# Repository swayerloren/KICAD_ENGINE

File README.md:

# KiCad Engine

AI-assisted KiCad workflow engine for using Codex or Claude inside VS Code with your existing KiCad app.

KiCad Engine is a repo you can download, open in VS Code, and give to Codex or Claude so the AI agent has structured rules, prompts, tools, and workflows for working on KiCad schematic and PCB projects. It is designed for people who already like KiCad and want AI assistance without switching to Flux or another paid PCB design platform.

The repo is the AI-agent operating system for KiCad work. It gives the agent a repeatable workspace, startup rules, task contracts, validation gates, and project structure so it can help with real KiCad projects without depending on hidden local folders or improvised workflow assumptions.

Historical reports may still show original local paths; current work must use repo-relative paths and live discovery on the user's machine.

## Fast Start: ZIP -> VS Code -> One Prompt

1. Download the repo ZIP from GitHub.
2. Extract it.
3. Open the `KICAD_ENGINE` folder in VS Code.
4. Open Codex or Claude in that workspace.
5. Paste this minimal prompt:

```text
Read START_HERE_FOR_AI_AGENTS.md and route yourself correctly. Use the task router automatically if I do not provide a giant read-first list. Do not edit KiCad schematic or PCB files until the active project, task type, and relevant gates are confirmed. Summarize the current repo/project status and ask what task to run next.
```

Useful follow-up docs:

- [ONE_PROMPT_START.md](ONE_PROMPT_START.md)
- [DOWNLOAD_ZIP_START_HERE.md](DOWNLOAD_ZIP_START_HERE.md)
- [START_HERE.md](START_HERE.md)
- [CURRENT_STATUS.md](CURRENT_STATUS.md)
- [PROJECTS_INDEX.md](PROJECTS_INDEX.md)
- [WORKFLOWS_INDEX.md](WORKFLOWS_INDEX.md)
- [TOOLS_INDEX.md](TOOLS_INDEX.md)
- [03_TOOLS/TOOLS_INDEX.md](03_TOOLS/TOOLS_INDEX.md)
- [EXTERNAL_DEPENDENCIES.md](EXTERNAL_DEPENDENCIES.md)
- [LOCAL_SETUP_REQUIREMENTS.md](LOCAL_SETUP_REQUIREMENTS.md)
- [docs/PATH_PORTABILITY.md](docs/PATH_PORTABILITY.md)
- [docs/HEALTH_CHECK.md](docs/HEALTH_CHECK.md)

## Optional Open-Source Tool Integrations

KiCad Engine now includes a first-party optional-tool integration layer under
[`03_TOOLS/open_source_integrations`](03_TOOLS/open_source_integrations/README.md).

- It documents approved upstream tools and their licenses.
- It keeps the default ZIP download usable without large bundled payloads.
- It provides dry-run install wrappers and a read-only verification script.
- It does not vendor upstream repos, `node_modules`, virtual environments, or
  large binaries by default.

Useful entry points:

- [`03_TOOLS/open_source_integrations/TOOL_REGISTRY.md`](03_TOOLS/open_source_integrations/TOOL_REGISTRY.md)
- [`03_TOOLS/open_source_integrations/TOOLS_APPROVED_FOR_LOCAL_USE.md`](03_TOOLS/open_source_integrations/TOOLS_APPROVED_FOR_LOCAL_USE.md)
- [`setup/verify_optional_kicad_tools.py`](setup/verify_optional_kicad_tools.py)

## What KiCad Engine Is

KiCad Engine is an AI-agent rule and workflow engine for KiCad work.

- It helps Codex and Claude work in a predictable, auditable way.
- It gives AI agents project structure, task contracts, routing rules, DRC/ERC expectations, manufacturing checklists, and validation workflows.
- It is designed to work with the user's existing local KiCad installation.
- It supports project creation, review, cleanup, validation, documentation, and release-prep workflows around KiCad projects.
- It helps the AI agent operate inside a real repo instead of improvising from memory.

## What KiCad Engine Is Not

- It is not a replacement for KiCad.
- It is not an automatic perfect PCB designer.
- It is not a guarantee of fabrication-ready boards.
- It is not a cloud SaaS PCB tool.

## How It Works

- The AI agent reads `00_CODEX_START/` before doing project work.
- The AI agent follows task contracts so docs-only, audit-only, and edit-required work are separated clearly.
- The AI agent works inside `04_KICAD_PROJECTS/` for real project context.
- The AI agent uses tools in `03_TOOLS/` and workflows in `09_ACCURACY_ENGINE/` and `14_LAYOUT_AUTOMATION/`.
- The AI agent produces auditable changes, reports, DRC/ERC results, live-state summaries, and visual-review records instead of making silent broad edits.

## Project Workspace

`04_KICAD_PROJECTS/active`

- current working KiCad projects

`04_KICAD_PROJECTS/archive`

- older, reference, demo, or historical KiCad projects

`04_KICAD_PROJECTS/templates`

- starting templates for new projects

## Using Your Own KiCad Project

1. Create a new folder under `04_KICAD_PROJECTS/active`.
2. Put or create your KiCad project files there.
3. Ask Codex or Claude to read `00_CODEX_START/` and create, review, or organize the project.
4. Use the repo's workflow gates, routing rules, validation scripts, and report structure as the operating framework for that project.

## Routing Rules

- avoid 90-degree bends
- prefer 45-degree bends or smooth curves
- acute angles are not allowed
- no ugly zig-zag routing
- no bad pad-entry geometry
- no antenna keepout violations
- no blind autoroute without audit
- DRC quiet does not mean visually or professionally acceptable

## Manufacturing Support

KiCad Engine includes workflow support for manufacturing preparation and review around:

- JLCPCB
- PCBWay
- Gerbers
- drill files
- BOM
- CPL / pick-and-place

Fabrication outputs still require human review before anything is treated as order-ready.

## Repo Map

| Folder | Purpose |
| --- | --- |
| `00_CODEX_START` | AI startup instructions |
| `03_TOOLS` | scripts and tool helpers |
| `04_KICAD_PROJECTS` | KiCad project workspace |
| `09_ACCURACY_ENGINE` | validation and gates |
| `14_LAYOUT_AUTOMATION` | placement/routing logic |
| `24_FAB_PROFILES` | fab/export profiles |
| `34_PCB_LAYOUT_SANDBOX` | planning and variants |
| `docs` | user/developer docs |

## Current Example Project

The repo currently includes `ESP32_CSI_WIFI_NODE` as an active example workspace. It is there to demonstrate how KiCad Engine organizes and reviews a live project. It is not the identity of the repo, and it is not fabrication-ready unless that project's own reports say so.

## Requirements

Required:

- VS Code or equivalent editor
- Codex or Claude access
- KiCad installed locally for schematic/PCB GUI work

Recommended:

- Python
- Git

Optional:

- GitHub CLI
- Codespaces
- FreeRouting or KiBot if configured

## Safety Notice

Human KiCad review is required before ordering PCBs.

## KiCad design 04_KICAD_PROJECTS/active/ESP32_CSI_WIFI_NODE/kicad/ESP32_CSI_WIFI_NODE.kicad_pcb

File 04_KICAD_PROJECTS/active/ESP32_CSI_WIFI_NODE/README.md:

# ESP32_CSI_WIFI_NODE

Active KiCad project workspace for an ESP32-based CSI/Wi-Fi node board.

## Status

- Project name: `ESP32_CSI_WIFI_NODE`
- Project path: `C:\Users\LJ\GitHub\KICAD_ENGINE\04_KICAD_PROJECTS\active\ESP32_CSI_WIFI_NODE`
- Active project selected in: [00_CODEX_START/CURRENT_PROJECT.md](../../../00_CODEX_START/CURRENT_PROJECT.md)
- Design status: `LIVE_PCB_EXISTS_NOT_FAB_READY`
- Fabrication status: `NOT_FINAL`

## Current Live PCB State

- KiCad PCB exists: `YES`
- Board outline exists: `YES`
- Footprints: `43`
- Tracks: `74`
- Vias: `32`
- Zones: `2`
- DRC: `0` violations, `17` unconnected items
- Detectable unrouted nets: `/DM_C`, `/DM_E`, `/DP_C`, `/DP_E`

## Primary Paths

- KiCad source: `kicad/`
- Reports: `reports/`
- Visual review: `_verification/pcb_visual/`
- Project memory: `memory/`
- Project history: `history/`
- Routing rehearsal work: `routing_work/`

## Current Review Entry Points

- [memory/CURRENT_PROJECT_STATE.md](memory/CURRENT_PROJECT_STATE.md)
- [memory/CURRENT_BLOCKERS.md](memory/CURRENT_BLOCKERS.md)
- [reports/FINAL_PCB_VISUAL_REVIEW_PACKET.md](reports/FINAL_PCB_VISUAL_REVIEW_PACKET.md)
- [reports/LJ_FINAL_PCB_REVIEW_CHECKLIST.md](reports/LJ_FINAL_PCB_REVIEW_CHECKLIST.md)

## Warning

This project is not fabrication-ready. USB data routing and other connectivity review work remain open, and the current visual-review packet is for human inspection, not manufacturing approval.

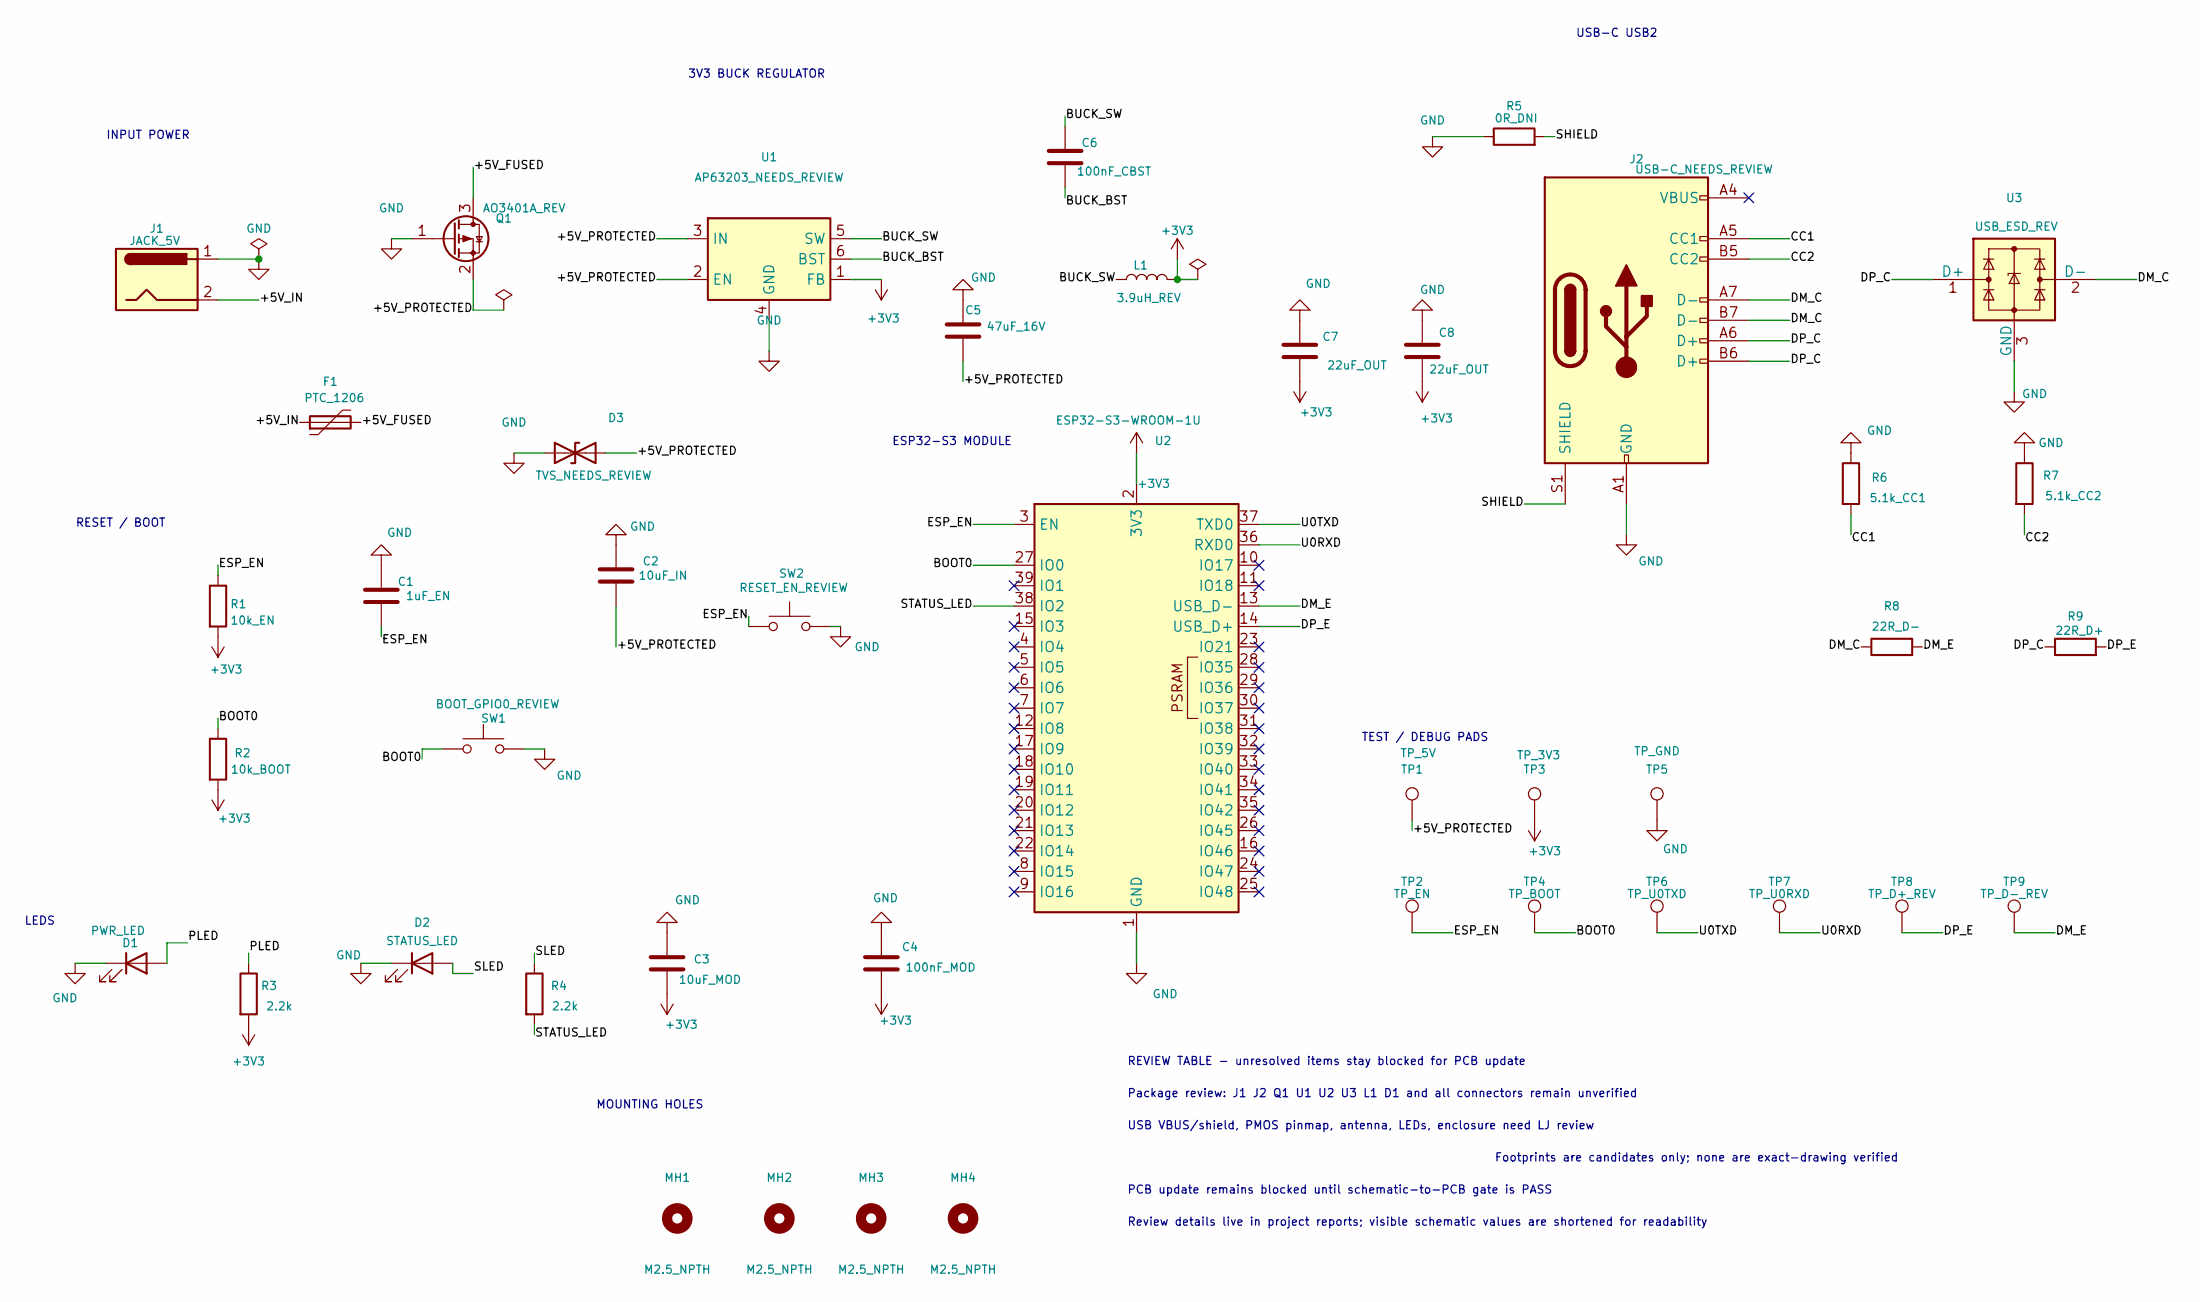
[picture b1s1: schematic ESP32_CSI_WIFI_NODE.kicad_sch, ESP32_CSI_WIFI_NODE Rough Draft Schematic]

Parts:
C1: 1uF_EN; C_0603_1608Metric
C2: 10uF_IN; C_0805_2012Metric
C3: 10uF_MOD; C_0805_2012Metric
C4: 100nF_MOD; C_0603_1608Metric
C5: 47uF_16V; C_1206_3216Metric
C6: 100nF_CBST; C_0603_1608Metric
C7, C8: 22uF_OUT; C_1206_3216Metric
D1: PWR_LED; LED_0603_1608Metric
D2: STATUS_LED; LED_0603_1608Metric
D3: TVS_NEEDS_REVIEW; D_SMA
F1: PTC_1206; Fuse_1206_3216Metric
J1: JACK_5V; BarrelJack_CUI_PJ-102AH_Horizontal
J2: USB-C_NEEDS_REVIEW; USB_C_Receptacle_GCT_USB4105-xx-A_16P_TopMnt_Horizontal
L1: 3.9uH_REV; L_Vishay_IFSC-1515AH_4x4x1.8mm
MH1, MH2, MH3, MH4: M2.5_NPTH; MountingHole_2.7mm_M2.5
Q1: AO3401A_REV; SOT-23
R1: 10k_EN; R_0603_1608Metric
R2: 10k_BOOT; R_0603_1608Metric
R3, R4: 2.2k; R_0603_1608Metric
R5: 0R_DNI; R_0603_1608Metric
R6: 5.1k_CC1; R_0603_1608Metric
R7: 5.1k_CC2; R_0603_1608Metric
R8: 22R_D-; R_0603_1608Metric
R9: 22R_D+; R_0603_1608Metric
SW1: BOOT_GPIO0_REVIEW; Panasonic_EVQPUJ_EVQPUA
SW2: RESET_EN_REVIEW; Panasonic_EVQPUJ_EVQPUA
TP1: TP_5V; TestPoint_Pad_D1.5mm
TP2: TP_EN; TestPoint_Pad_D1.5mm
TP3: TP_3V3; TestPoint_Pad_D1.5mm
TP4: TP_BOOT; TestPoint_Pad_D1.5mm
TP5: TP_GND; TestPoint_Pad_D1.5mm
TP6: TP_U0TXD; TestPoint_Pad_D1.5mm
TP7: TP_U0RXD; TestPoint_Pad_D1.5mm
TP8: TP_D+_REV; TestPoint_Pad_D1.5mm
TP9: TP_D-_REV; TestPoint_Pad_D1.5mm
U1: AP63203_NEEDS_REVIEW; TSOT-23-6
U2: ESP32-S3-WROOM-1U; ESP32-S3-WROOM-1
U3: USB_ESD_REV; SOT-23-6

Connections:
+3V3: C3.2, C4.2, C7.2, C8.2, L1.2, R1.2, R2.2, R3.2, TP3.1, U1.1 (FB), U2.2 (3V3)
/+5V_FUSED: F1.2, Q1.3 (D)
/+5V_IN: F1.1, J1.2
/+5V_PROTECTED: C2.2, C5.2, D3.2 (A2), Q1.2 (S), TP1.1, U1.2 (EN), U1.3 (IN)
/BOOT0: R2.1, SW1.1, TP4.1, U2.27 (IO0)
/BUCK_BST: C6.2, U1.6 (BST)
/BUCK_SW: C6.1, L1.1, U1.5 (SW)
/CC1: J2.A5 (CC1), R6.2
/CC2: J2.B5 (CC2), R7.2
/DM_C: J2.A7 (D-), J2.B7 (D-), R8.1, U3.2 (D-)
/DM_E: R8.2, TP9.1, U2.13 (USB_D-)
/DP_C: J2.A6 (D+), J2.B6 (D+), R9.1, U3.1 (D+)
/DP_E: R9.2, TP8.1, U2.14 (USB_D+)
/ESP_EN: C1.2, R1.1, SW2.1, TP2.1, U2.3 (EN)
/PLED: D1.2 (A), R3.1
/SHIELD: J2.S1 (SHIELD), R5.2
/SLED: D2.2 (A), R4.1
/STATUS_LED: R4.2, U2.38 (IO2)
/U0RXD: TP7.1, U2.36 (RXD0)
/U0TXD: TP6.1, U2.37 (TXD0)
GND: C1.1, C2.1, C3.1, C4.1, C5.1, C7.1, C8.1, D1.1 (K), D2.1 (K), D3.1 (A1), J1.1, J2.A1 (GND), J2.A12 (GND), J2.B1 (GND), J2.B12 (GND), Q1.1 (G), R5.1, R6.1, R7.1, SW1.2, SW2.2, TP5.1, U1.4 (GND), U2.1 (GND), U2.40 (GND), U2.41 (GND), U3.3 (GND)

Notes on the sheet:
INPUT POWER
REVIEW TABLE - unresolved items stay blocked for PCB update
3V3 BUCK REGULATOR
Package review: J1 J2 Q1 U1 U2 U3 L1 D1 and all connectors remain unverified
ESP32-S3 MODULE
USB VBUS/shield, PMOS pinmap, antenna, LEDs, enclosure need LJ review
RESET / BOOT
USB-C USB2
Footprints are candidates only; none are exact-drawing verified
LEDS
TEST / DEBUG PADS
MOUNTING HOLES
PCB update remains blocked until schematic-to-PCB gate is PASS
Review details live in project reports; visible schematic values are shortened for readability

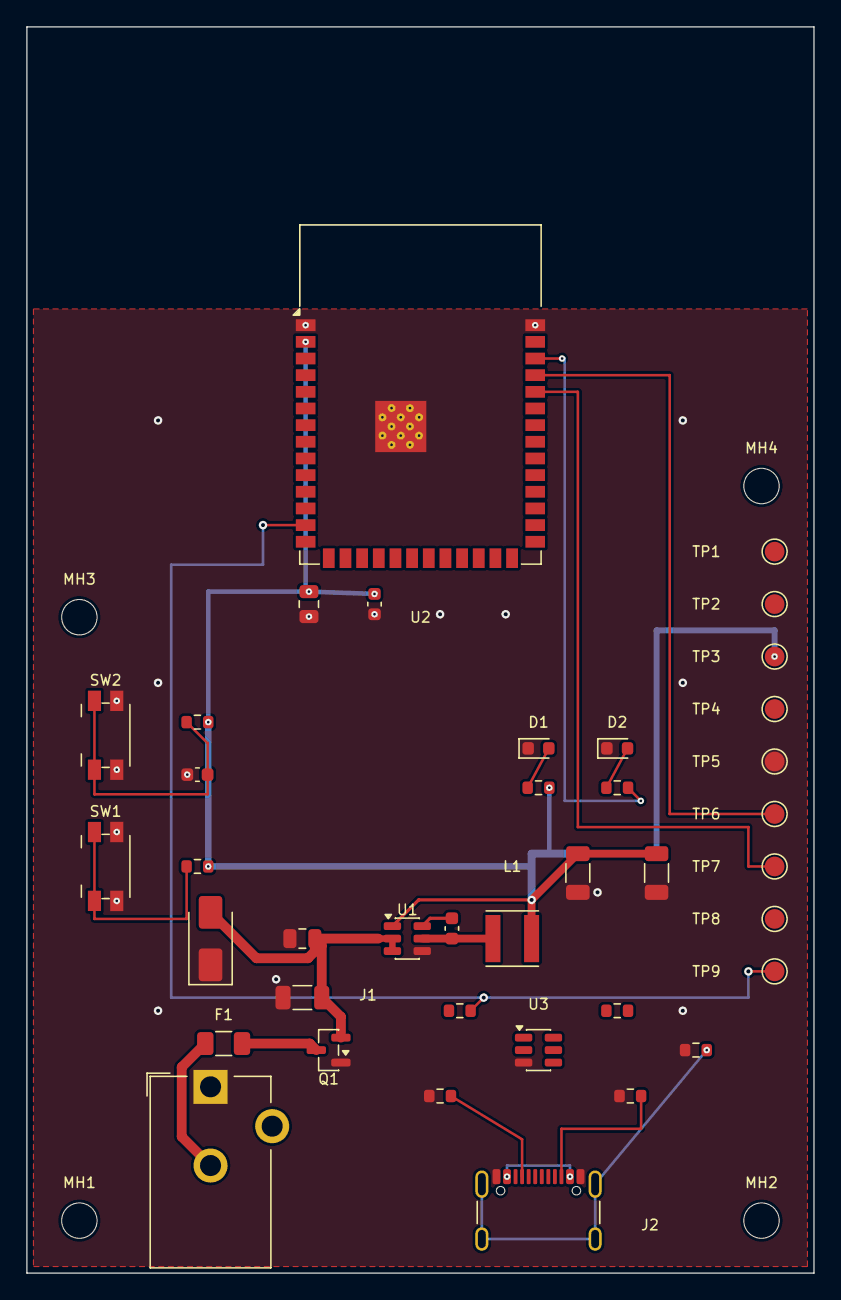
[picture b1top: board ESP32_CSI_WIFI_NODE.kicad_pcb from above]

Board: 2 copper layers, 60.0 x 95.0 mm, 43 parts (0 on the bottom side), 21 nets.

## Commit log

2026-05-08 Initial KiCad Engine workspace commit
2026-05-08 Add GitHub push report and closeout logs
2026-05-08 Add GitHub repo navigation and index layer
2026-05-08 Add GitHub indexing reports and closeout artifacts
2026-05-08 Add GitHub repo index and navigation docs
2026-05-08 Add task-type execution contract for PCB work
2026-05-08 Promote live KiCad state as gate authority
2026-05-08 Add hard-fail routing geometry checks
2026-05-08 Add placement readiness scoring before routing
2026-05-08 Add staged routing runner and no-progress detector
2026-05-08 Record hardening PR artifacts
2026-05-08 Update GitHub README and repo documentation
2026-05-08 Add GitHub dev infrastructure and Codespaces setup
2026-05-08 Add GitHub Actions and branch workflow docs
2026-05-08 Save latest repo documentation and infrastructure updates
2026-05-08 Record direct main update closeout
2026-05-08 Add v0.1.0 release notes
2026-05-08 Record v0.1.0 release closeout
2026-05-08 Record simple main cleanup
2026-05-08 Clarify repo purpose and local VS Code usage
2026-05-08 Document local-only tool folders
2026-05-08 Improve repo portability and local AI-agent setup docs
2026-05-08 Audit and harden ZIP portability and local toolchain setup
2026-05-08 Rewrite README around KiCad Engine one-prompt workflow
2026-05-08 Refocus README on KiCad Engine identity
2026-05-09 Remove tracked routing scratch payload from portable repo
2026-05-09 Remove machine-local generated KiCad library indexes
2026-05-09 Clarify machine-specific tool inventory
2026-05-09 Document historical local paths as non-portable evidence
2026-05-09 Add KiCad Python context handling for pcbnew workflows
2026-05-09 Add final portability verification report
2026-05-09 Rename README.md to github_README.md
2026-05-09 Repair ESP32 CSI WiFi node PCB routing
2026-05-12 Update KiCad Engine knowledge base and migration indexes
2026-05-12 repair startup router and release readiness gates
2026-05-15 strengthen schematic human drafting rules
